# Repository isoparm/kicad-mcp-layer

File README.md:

# kicad-mcp-layer

An AI layer for KiCad 10: a Model Context Protocol server that lets Claude Code, or any MCP
client, work on KiCad designs.

It drives KiCad through three channels and says which one it is using:

| Channel | Mechanism | Used for |
|---|---|---|
| `cli` | `kicad-cli` subprocess | ERC, DRC, netlists, BOM, renders, fabrication exports. Works with KiCad open or closed. |
| `ipc` | KiCad's official IPC API via `kicad-python` | The board open in the PCB editor. Edits land as undo steps. |
| `file` | Lossless edits of `.kicad_sch` and `.kicad_pro` | Schematics, which KiCad 10 exposes no API for. |

The legacy SWIG `pcbnew` module is never used; a test enforces it.

This is the library half of **[kicad-ai-stack](https://github.com/ShamanAndrey/kicad-ai-stack)**, the
workspace it was built in. The stack adds the one-command setup (`bootstrap.py`, which clones this
repository, builds its environment and registers the server with Claude Code) and the working rules for
a session. Start there if you want the whole thing set up; start here if you want the server or the
design package on their own.

## What this is

Two layers on one core.

* **`kicad_layer.design` is the product.** A board is Python data: parts from a catalogue, a
  signal table, circuits as pin-to-net statements, placement, saved copper. The KiCad files are
  build outputs, and KiCad's own ERC and DRC are the tests. Two boards live on it.
* **The MCP server is its check-and-view layer** for Claude Code: checks, exports, renders,
  reviews, documentation and library search. That is the `core` tool tier, registered by
  default. The `full` tier adds the schematic and board edit tools and the routers.

A project holds only its data: sheets as circuits, placement, a `Project`, a routing plan for the
pipeline in `kicad_layer.routers`, and the fabrication package from `kicad_layer.design.fab`. The whole
authoring API is on one generated sheet, [docs/design-api.md](docs/design-api.md), so a session reads
that instead of the source; `python -m kicad_layer.design.inspect` answers questions about a built board.

The routers (`kicad_layer.routers`) are frozen: fixes, not features. The intended loop routes by
hand in KiCad and keeps the copper as data. `tests/test_layers.py` enforces the layering.

## Status

Pre-alpha, built in the open. Done so far:

* Rung 0: environment diagnostics, the capability matrix, project discovery, workspace
  confinement, read-only default mode.
* Rung 1: every kicad-cli tool (ERC, DRC, netlist, trace, BOM, fabrication export, board
  render, schematic render).
* Rung 2: reading the board open in KiCad's PCB Editor over the IPC API (summary, items,
  per-net statistics), with every failure classified as unreachable or rejected.
* Writers: a lossless S-expression engine, a library loader, and schematic and board
  writers that generated a complete 89-LED board which passed ERC and DRC with zero
  findings (`examples/hello_world`).
* Milestone 1: a full-text index of every library KiCad can
  see, including a project's own, with `lib_search`, `sym_info`, `fp_info` and `lib_index`.
* Milestone 2: editing existing schematics losslessly. A concrete syntax tree keeps every
  untouched byte; edits are atomic, snapshotted, refused while KiCad holds the lock, and
  validated by ERC and a netlist comparison. Tools: `sch_list_components`, `sch_get_symbol`,
  `sch_set_property`, `sch_add_component`, `sch_wire`, `sch_label`, `sch_mark`, `sch_delete`,
  `sch_annotate`.

* Milestone 3: editing boards. Live through KiCad's API as one undo step per operation,
  read back from KiCad; or losslessly in the file when the board is closed. A board seen
  live is never edited on disk. Tools: `pcb_place_footprint`, `pcb_move_footprint`,
  `pcb_add_track`, `pcb_add_via`, `pcb_add_zone`, `pcb_refill_zones`, `pcb_delete_items`,
  `pcb_save`. KiCad 10's own "create items from text" call is a stub, so live placement
  builds the footprint from the library file pad by pad.

* Milestone 4: design review beyond DRC. `review_board`, `review_schematic` and
  `review_project` produce one report where every check says PASS, WARN, FAIL, INFO or
  UNVERIFIED with its evidence and the source of its limits: DRC and unrouted connections,
  zone fill state, parts outside the outline, manufacturability against JLCPCB's published
  limits, track widths on power nets, zone stitching, decoupling distance, footprints and
  values and annotation, power-net sources, and the honest state of SPICE. The first run
  on the Hello World found its vias below the fab's minimum annular ring, which is why the
  layer's default via is now 0.8 mm. The first run on a real project then caught the review
  itself: PWR_FLAGs never appear in the exported netlist, so the power-source check now
  follows KiCad's ERC rule instead. Checks are documented in
  [docs/review-checks.md](docs/review-checks.md).

* Writers, second round, for the first real product (a Compute Module 5 carrier): hierarchical
  schematics (sheet symbols with pins, hierarchical labels, per-sheet instance paths, multi-unit
  symbols), boards with any even number of copper layers, and project-local symbol and
  footprint libraries. A seven-sheet, four-layer project generated this way passes ERC with
  no findings; KiCad's own ERC and DRC are the tests.

* Documentation layer: `doc_fetch`, `doc_import`, `doc_list`, `doc_text` and `doc_page` keep
  datasheets and reference designs in an indexed library under `research/references` with
  their source URL, date and hash, extract text per page, and render pages to images so
  pinouts, package drawings and tables can be read. When a site answers with a scripted
  download portal or refuses the plain client, an optional headless-Chromium tier
  (`pip install "kicad-mcp-layer[browser]"`) loads the page and takes the download it offers;
  what still fails gets a classified error that says to save the file in a browser and import it.

* Routing checks and parts: `route_check` measures every differential pair on a board (lengths,
  skew against the interface's limit, coupled share, class gap and width, layer changes) and the
  review carries it as `diff_pairs`; `impedance_calc` and `stackup_info` give closed-form estimates
  next to the fab's published geometries for JLCPCB's 4-layer stack-up; `parts_search` checks
  JLCPCB's assembly catalogue for LCSC codes and stock. The first real board's 28 pairs and 30
  special parts went through them before routing started.

* Routing: `route_pairs` routes differential pairs as coupled pairs (escapes planned and reserved
  for every pair first, a heading-aware search that never folds a pair back on itself, mitred
  offsets, a two-via crossover where P would land on the wrong side, tuning bumps for skew);
  `stitch_planes` drops a stub and via from every surface-mount pad on a plane net; `autoroute`
  hands the rest to FreeRouting through a Specctra DSN with the earlier copper protected and
  merges the session back. All three write a routes JSON next to the board rather than touching
  the board, so a design-as-code project re-applies it on every build. The first real board's 21
  routed pairs came out with zero clearance errors; the residual skew sits on the pairs that
  needed a crossover.

* Manufacturing package (milestone 5, PCBWay): `kicad_layer.design.fab` writes the Gerber and drill
  archive, the position file and a BOM in PCBWay's assembly layout from a finished build, and refuses
  a BOM line without a part number. The first real product ordered from it.

* The design package became the product: `kicad_layer.design` holds a board as data (sheets described
  as circuits with a layout plan, a signal table that drives the module sheet and the root, a project
  with its rule set, placements, blocks) and the KiCad files are build outputs. A build writes the
  schematic, the project file with its constraints and net classes, the design rules, runs ERC, exports
  the netlist and checks every sheet against its own description and against a reference netlist, pin
  group for pin group. Fab rule sets for JLCPCB and AISLER (constraints, classes on the fab's published
  pair geometries, its own `.kicad_dru` rules), and `review_board` takes a fab name for its limits.

* Hand layout on a generated schematic: for a board placed and routed by a person in KiCad, the build
  never writes the board. `build.py --seed` writes its first import instead of KiCad's F8, every footprint
  in rows and linked to its symbol; blocks (an anchor footprint, members with offsets, one KiCad group)
  keep parts that belong together, applied by `--blocks`. The routers are frozen: fixes, not features.

* Parts and documents: `doc_sections` and `doc_facts` read a document's index and a part's fact sheet
  (written once from the datasheet, every number with its page); `lib_fetch` brings a symbol, footprint
  and 3D model for an LCSC code from EasyEDA's data, upgraded to KiCad's current format, for the pad-for-pad
  check against the drawing that follows.

Next: bring-up (milestone 6) and per-fab export profiles, driven by the first real product. See
[docs/tools.md](docs/tools.md) for the tool list.

## Requirements

* KiCad 10.0.x (built against 10.0.6, Windows 11). `kicad-cli` ships with it. Upgrade KiCad
  deliberately: the file formats and the API move with each major, `kicad_doctor` reports the
  drift, and the full test suite is the check.
* Python 3.12 or newer.
* `kicad-python` for the IPC channel (the board open in KiCad), as the `ipc` extra. Without it the
  doctor says so and every kicad-cli and file tool still works. Other extras: `parts` (easyeda2kicad
  behind `lib_fetch`), `preview` (PyMuPDF for sheet previews), `browser` (headless Chromium for
  datasheet portals), `dev` (pytest).
* Developed and tested on Windows 11; kicad-cli discovery also knows the macOS bundle and the Linux
  paths. One convenience is Windows-only: `build.py --open` starts KiCad through a scheduled task.

## Install

The quick way is the stack's bootstrap: clone [kicad-ai-stack](https://github.com/ShamanAndrey/kicad-ai-stack)
and run `python bootstrap.py`; it clones this repository next to it, creates the environment, installs the
extras and writes the Claude Code registration. On its own:

With [uv](https://docs.astral.sh/uv/):

```bash
uv sync --extra dev --extra ipc
uv run pytest
```

With pip:

```bash
python -m venv .venv
.venv\Scripts\python -m pip install -e ".[dev,ipc]"
.venv\Scripts\python -m pytest
```

The default run is the fast loop: in parallel, without the slow tests (a full library index, a
whole review, a headless browser) and without the live ones. `pytest -m "not gui"` adds the slow
tests; `pytest -m ""` runs everything and needs KiCad open with its API on. Tests that need
`kicad-cli` skip themselves when it is not installed.

## Register with Claude Code

Put a `.mcp.json` in the directory that holds your KiCad projects:

```json
{
  "mcpServers": {
    "kicad-mcp-layer": {
      "command": "C:\\path\\to\\kicad-mcp-layer\\.venv\\Scripts\\python.exe",
      "args": ["-m", "kicad_layer"],
      "env": {
        "KICAD_LAYER_WORKSPACE": "C:\\path\\to\\your\\kicad\\projects",
        "KICAD_LAYER_MODE": "readonly"
      }
    }
  }
}
```

Register it in one place only. If Claude Code runs inside the Claude desktop app, quit and
relaunch the app after changing MCP configuration; a new session is not enough.

## Configuration

| Variable | Default | Meaning |
|---|---|---|
| `KICAD_LAYER_WORKSPACE` | current directory | Every path must resolve under it |
| `KICAD_LAYER_MODE` | `readonly` | `write` allows design edits |
| `KICAD_CLI` | auto-detected | Explicit path to `kicad-cli`; if set and wrong, that is an error |
| `KICAD_API_SOCKET` | `ipc://%TEMP%\kicad\api.sock` | IPC address, honoured by `kicad-python` |
| `KICAD_LAYER_CACHE_DIR` | `%LOCALAPPDATA%\kicad-mcp-layer\cache` | Netlist and report cache |
| `KICAD_LAYER_LOG` | `INFO` | stderr log level |
| `KICAD_LAYER_TOOLS` | `core` | `core` registers checks, exports, renders, reviews, libraries, documents and board reads; `full` adds the design-edit tools and the routers |

To use the board tools, enable the API in KiCad: Preferences, Plugins, "Enable KiCad API". It
takes effect immediately.

## Design

The architecture decisions and the research behind them live in a companion `research/`
folder (not part of this package): a survey of every existing KiCad MCP server, KiCad 10's
file formats and API surface, and the tests that showed why no existing schematic parser
could be reused. Short version:

* Connectivity comes from `kicad-cli sch export netlist`, never from home-grown wire tracing.
* Every IPC failure is classified as unreachable or rejected; file edits are allowed only when
  unreachable, and never for a board this process has seen live.
* Schematic writes refuse while KiCad holds the editor lock file.
* Verdicts can say `UNVERIFIED`. A missing report is never a pass.
* Two tool tiers: `core` reads, checks, exports, renders, reviews and documents; `full` adds
  design edits and the frozen routers.

## A word to visitors

Everything here stands on KiCad. It is free, open source, and its development is funded by donations.
The KiCad developers have said what they want for the next release, and every item would let this
project grow: an API for the schematic editor, which KiCad 10 does not have, headless use of that API
through kicad-cli, and footprints generated through the API instead of the footprint wizard. Each one
would replace a workaround in this library with a direct call into KiCad.

If this project is useful to you, please visit [kicad.org](https://www.kicad.org/) and
[donate to KiCad](https://www.kicad.org/donate/). That is where the real work happens.

## Related

* [kicad-ai-stack](https://github.com/ShamanAndrey/kicad-ai-stack): the workspace around this library, with
  the setup script and the working rules for a Claude Code session.
* [examples/hello_world](examples/hello_world): a complete board as data on this library, the first one it built.
* [examples/two_layer_basic](examples/two_layer_basic): the smallest complete project on the design package
  (`Circuit`, `Layout`, `Board`, `Project`), a two-layer board.
* [docs/tools.md](docs/tools.md) the tool reference, [docs/design-api.md](docs/design-api.md) the authoring API.

## Acknowledgements

Ideas and, where MIT-licensed, code from
[kicad-mcp-pro](https://github.com/oaslananka/kicad-mcp-pro),
[kicad-happy](https://github.com/aklofas/kicad-happy),
[lamaalrajih/kicad-mcp](https://github.com/lamaalrajih/kicad-mcp) and
[KiCAD-MCP-Server](https://github.com/mixelpixx/KiCAD-MCP-Server); lessons from
[Konnect](https://github.com/mixelpixx/Konnect). Test fixtures are KiCad's own demo projects.

## License

MIT. See [LICENSE](LICENSE).

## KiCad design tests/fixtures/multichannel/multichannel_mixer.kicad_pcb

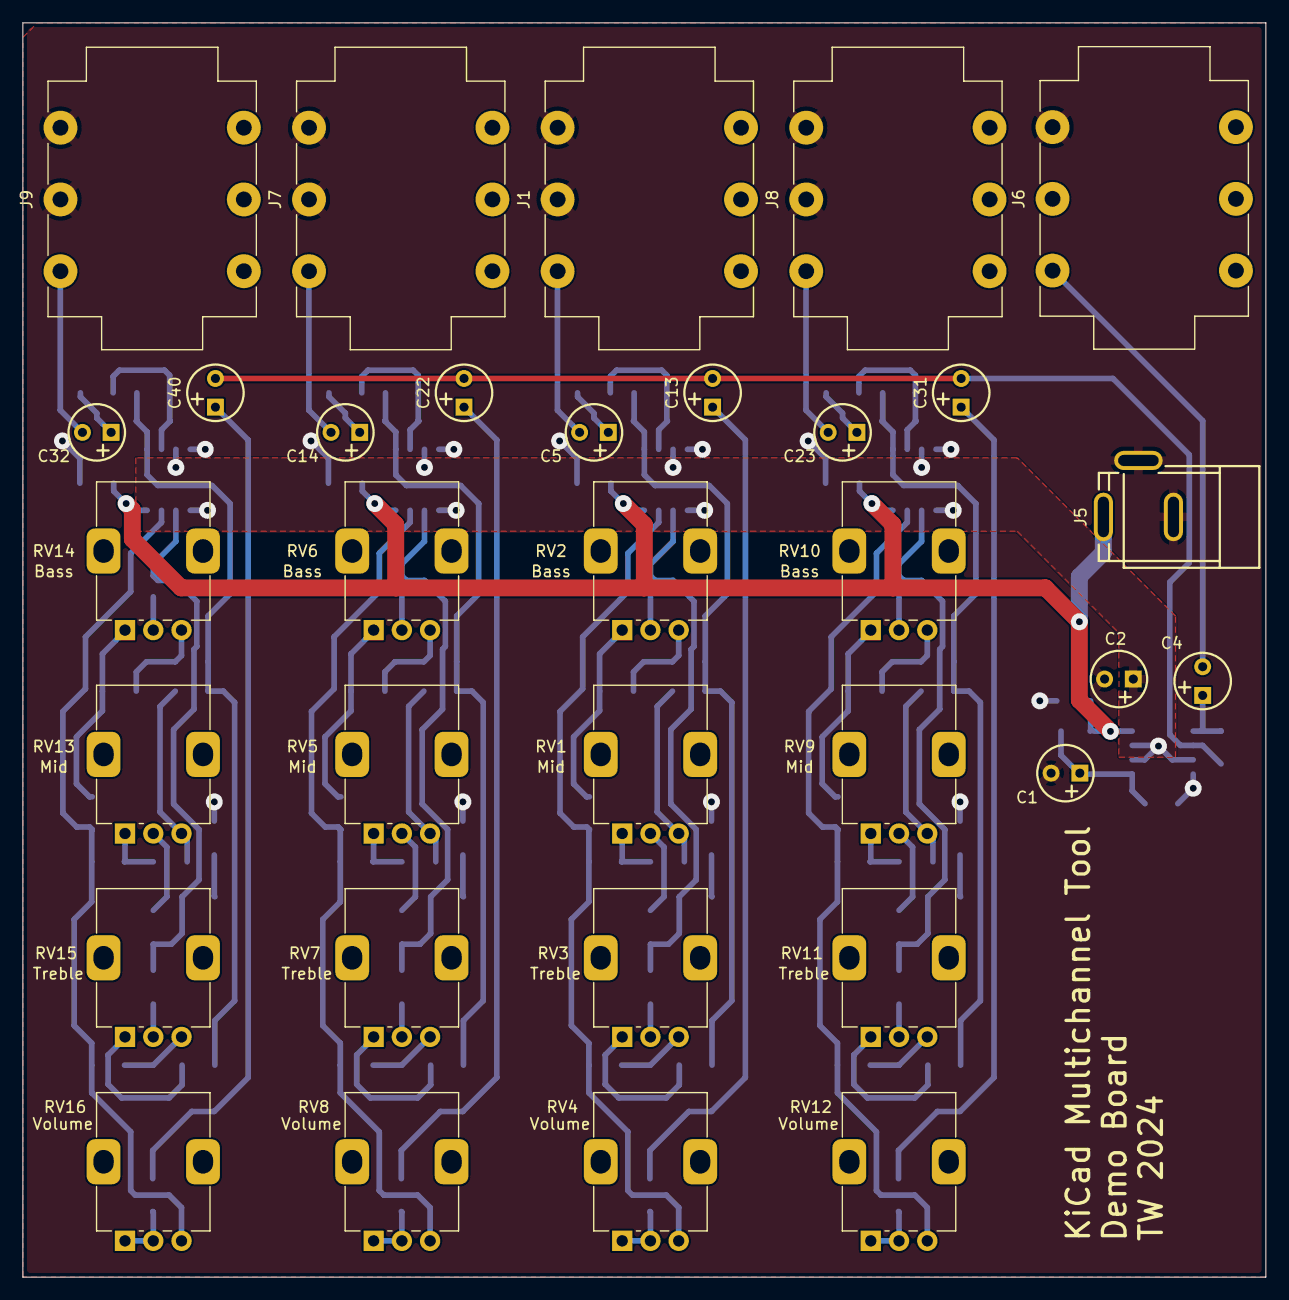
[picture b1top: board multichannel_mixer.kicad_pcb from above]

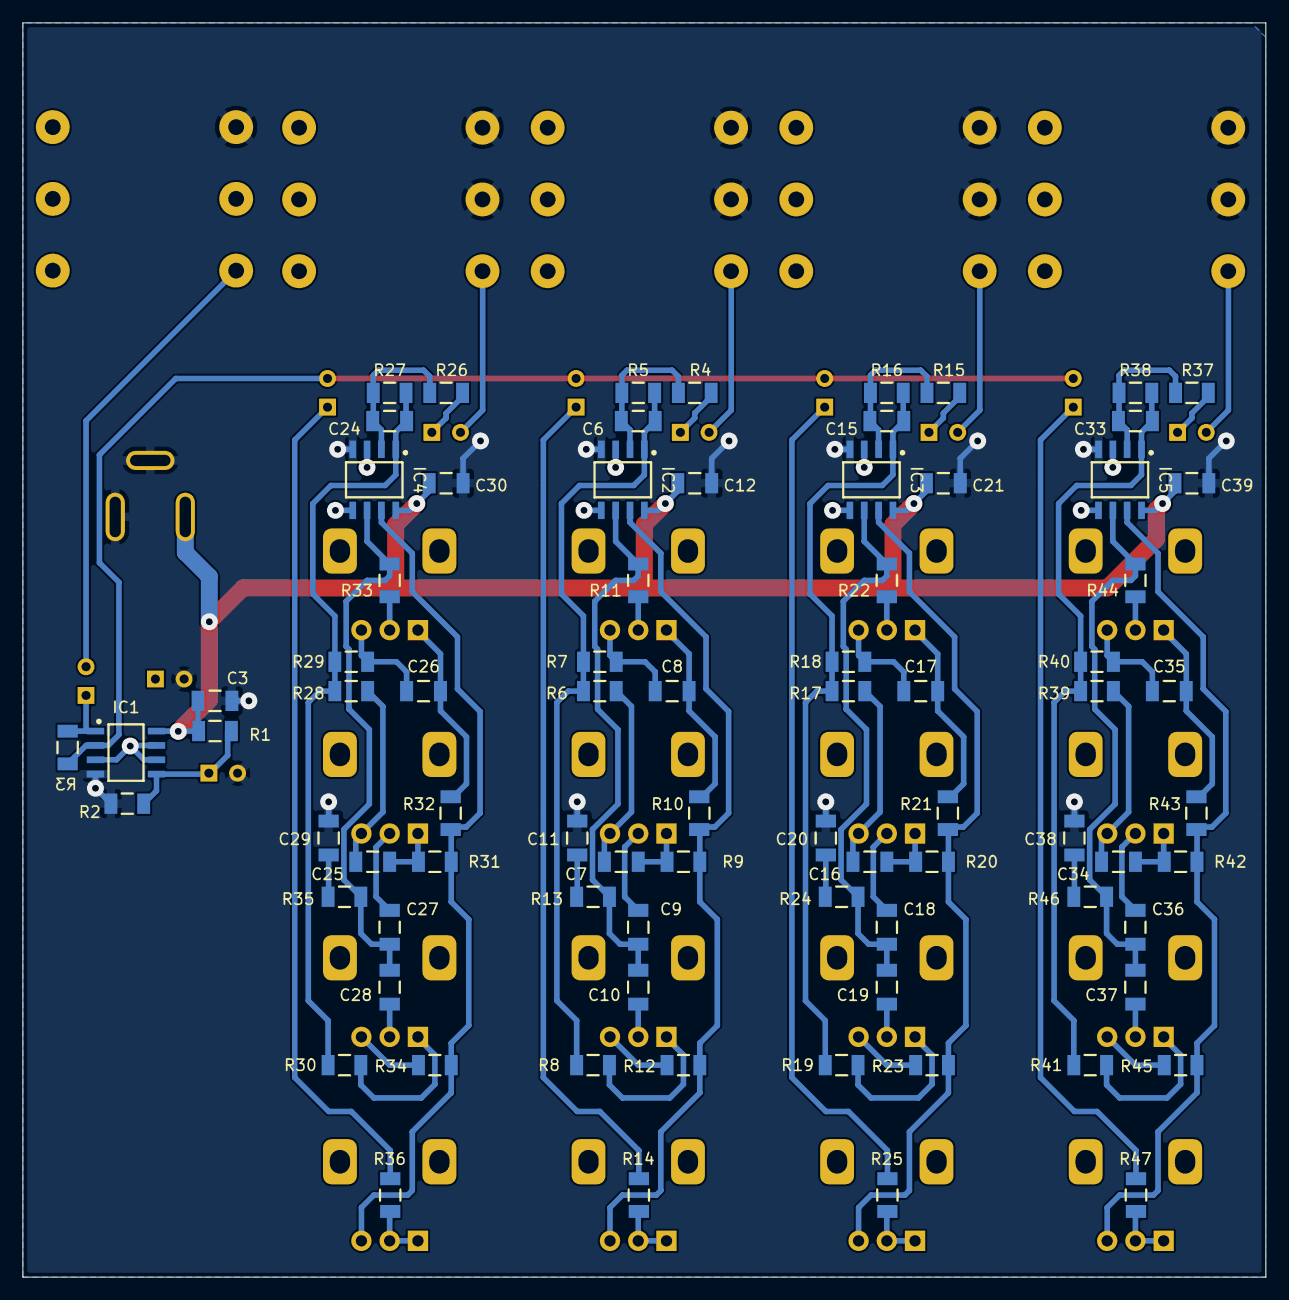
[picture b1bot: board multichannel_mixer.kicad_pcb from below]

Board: 2 copper layers, 110.0 x 111.0 mm, 114 parts (81 on the bottom side), 79 nets.

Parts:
C1, C2, C4, C5, C13, C14, C22, C23, C31, C32, C40: CTEB_2.2UF_35V_10%_254-500X840; CAPPRB254-500X840
C3, C6, C7, C8, C9, C10, C11, C12, C15, C16, C17, C18, C19, C20, C21, C24, C25, C26, C27, C28, C29, C30, C33, C34, C35, C36, C37, C38, C39: CC1206_100NF_50V_10%_X7R; CAPC3216X140N
IC1, IC2, IC3, IC4, IC5: TL072CD; SOIC127P600X175-8N
J1, J6, J7, J8, J9: CH1; Jack_6.35mm_Neutrik_NMJ6HCD2_Horizontal
J5: Power; CLIFF_FC68148(DC-10A)
R1, R2, R3, R4, R5, R6, R7, R8, R9, R10, R11, R12, R13, R14, R15, R16, R17, R18, R19, R20, R21, R22, R23, R24, R25, R26, R27, R28, R29, R30, R31, R32, R33, R34, R35, R36, R37, R38, R39, R40, R41, R42, R43, R44, R45, R46, R47: R1206_10K_1%_0.25W_100PPM; RESC3216X65N
RV1, RV5, RV9, RV13: Mid; Potentiometer_Alps_RK09K_Single_Vertical
RV2, RV6, RV10, RV14: Bass; Potentiometer_Alps_RK09K_Single_Vertical
RV3, RV7, RV11, RV15: Treble; Potentiometer_Alps_RK09K_Single_Vertical
RV4, RV8, RV12, RV16: Volume; Potentiometer_Alps_RK09K_Single_Vertical

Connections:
+12V: C3.2, C12.2, C21.2, C30.2, C39.2, IC1.8 (V+), IC2.8 (V+), IC3.8 (V+), IC4.8 (V+), IC5.8 (V+), J5.1, R1.2
/CH1/OUT: C13.2, C22.2, C31.2, C40.2, IC1.2 (IN-), R3.1
GND: C1.2, C2.2, C3.1, C11.1, C12.1, C20.1, C21.1, C29.1, C30.1, C38.1, C39.1, IC1.4 (V-), IC2.4 (V-), IC3.4 (V-), IC4.4 (V-), IC5.4 (V-), J1.R, J1.S, J5.2, J5.3, J6.S, J7.R, J7.S, J8.R, J8.S, J9.R, J9.S, R2.1
unnamed: C4.2, J6.T
unnamed: C5.1, R4.1
unnamed: C5.2, J1.T
unnamed: C7.1, R6.2, RV1.3
unnamed: C7.2, R9.1, RV1.1
unnamed: C8.1, R7.2, RV2.3
unnamed: C8.2, R10.1, RV2.1
unnamed: C9.1, RV1.2
unnamed: C10.1, RV3.2
unnamed: C11.2, R13.1
unnamed: C13.1, R14.2
unnamed: C14.1, R15.1
unnamed: C14.2, J7.T
unnamed: C16.1, R17.2, RV5.3
unnamed: C16.2, R20.1, RV5.1
unnamed: C17.1, R18.2, RV6.3
unnamed: C17.2, R21.1, RV6.1
unnamed: C18.1, RV5.2
unnamed: C19.1, RV7.2
unnamed: C20.2, R24.1
unnamed: C22.1, R25.2
unnamed: C23.1, R26.1
unnamed: C23.2, J8.T
unnamed: C25.1, R28.2, RV9.3
unnamed: C25.2, R31.1, RV9.1
unnamed: C26.1, R29.2, RV10.3
unnamed: C26.2, R32.1, RV10.1
unnamed: C27.1, RV9.2
unnamed: C28.1, RV11.2
unnamed: C29.2, R35.1
unnamed: C31.1, R36.2
unnamed: C32.1, R37.1
unnamed: C32.2, J9.T
unnamed: C34.1, R39.2, RV13.3
unnamed: C34.2, R42.1, RV13.1
unnamed: C35.1, R40.2, RV14.3
unnamed: C35.2, R43.1, RV14.1
unnamed: C36.1, RV13.2
unnamed: C37.1, RV15.2
unnamed: C38.2, R46.1
unnamed: C40.1, R47.2
unnamed: C4.1, IC1.1 (OUT), R3.2
unnamed: C1.1, IC1.5 (IN+), R1.1, R2.2
unnamed: C6.1, IC2.2 (IN-), R4.2, R5.1
unnamed: C6.2, IC2.1 (OUT), R5.2, R6.1, R7.1, R8.2
unnamed: C9.2, C10.2, IC2.6 (IN-), R11.2, R13.2
unnamed: IC2.7 (OUT), R9.2, R10.2, R12.1, RV4.3
unnamed: C15.1, IC3.2 (IN-), R15.2, R16.1
unnamed: C15.2, IC3.1 (OUT), R16.2, R17.1, R18.1, R19.2
unnamed: C18.2, C19.2, IC3.6 (IN-), R22.2, R24.2
unnamed: IC3.7 (OUT), R20.2, R21.2, R23.1, RV8.3
unnamed: C24.1, IC4.2 (IN-), R26.2, R27.1
unnamed: C24.2, IC4.1 (OUT), R27.2, R28.1, R29.1, R30.2
unnamed: C27.2, C28.2, IC4.6 (IN-), R33.2, R35.2
unnamed: IC4.7 (OUT), R31.2, R32.2, R34.1, RV12.3
unnamed: C33.1, IC5.2 (IN-), R37.2, R38.1
unnamed: C33.2, IC5.1 (OUT), R38.2, R39.1, R40.1, R41.2
unnamed: C36.2, C37.2, IC5.6 (IN-), R44.2, R46.2
unnamed: IC5.7 (OUT), R42.2, R43.2, R45.1, RV16.3
unnamed: R8.1, RV3.1
unnamed: R11.1, RV2.2
unnamed: R12.2, RV3.3
unnamed: R14.1, RV4.1, RV4.2
unnamed: R19.1, RV7.1
unnamed: R22.1, RV6.2
unnamed: R23.2, RV7.3
unnamed: R25.1, RV8.1, RV8.2
unnamed: R30.1, RV11.1
unnamed: R33.1, RV10.2
unnamed: R34.2, RV11.3
unnamed: R36.1, RV12.1, RV12.2
unnamed: R41.1, RV15.1
unnamed: R44.1, RV14.2
unnamed: R45.2, RV15.3
unnamed: R47.1, RV16.1, RV16.2
vbias: C2.1, IC1.3 (IN+), IC1.6 (IN-), IC1.7 (OUT), IC2.3 (IN+), IC2.5 (IN+), IC3.3 (IN+), IC3.5 (IN+), IC4.3 (IN+), IC4.5 (IN+), IC5.3 (IN+), IC5.5 (IN+)

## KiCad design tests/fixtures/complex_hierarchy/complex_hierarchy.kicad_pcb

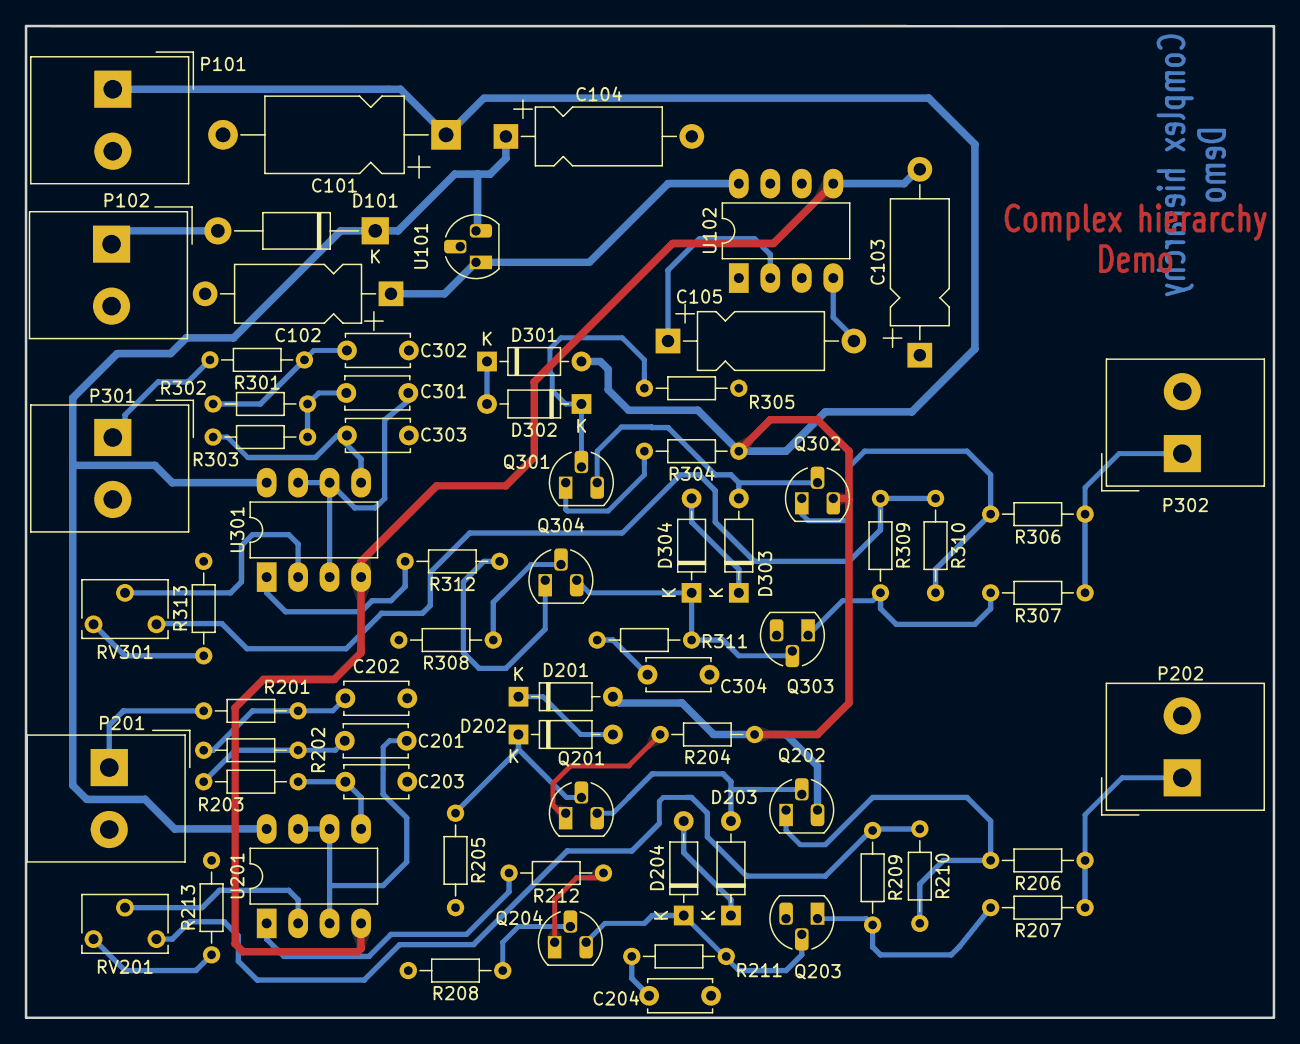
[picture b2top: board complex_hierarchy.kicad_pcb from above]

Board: 2 copper layers, 100.7 x 80.0 mm, 68 parts (0 on the bottom side), 50 nets.

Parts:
C101: 47uF/63V; CP_Axial_L11.0mm_D6.0mm_P18.00mm_Horizontal
C102: 47uF; CP_Axial_L10.0mm_D4.5mm_P15.00mm_Horizontal
C103, C105: 10uF; CP_Axial_L10.0mm_D4.5mm_P15.00mm_Horizontal
C104: 47uF/20V; CP_Axial_L10.0mm_D4.5mm_P15.00mm_Horizontal
C201, C301: 15nF; C_Disc_D5.0mm_W2.5mm_P5.00mm
C202, C302: 150nF; C_Disc_D5.0mm_W2.5mm_P5.00mm
C203, C303: 4.7nF; C_Disc_D5.0mm_W2.5mm_P5.00mm
C204, C304: 820pF; C_Disc_D5.0mm_W2.5mm_P5.00mm
D101: 1N4007; D_DO-41_SOD81_P12.70mm_Horizontal
D201, D202, D203, D204, D301, D302, D303, D304: 1N4148; D_DO-35_SOD27_P7.62mm_Horizontal
P101, P102, P201, P202, P301, P302: CONN_2; Altech_AK300_1x02_P5.00mm_45-Degree
Q201, Q203, Q301, Q303: MPSA92; TO-92_HandSolder
Q202, Q204, Q302, Q304: MPSA42; TO-92_HandSolder
R201, R208, R212, R301, R308, R312: 1K; R_Axial_DIN0204_L3.6mm_D1.6mm_P7.62mm_Horizontal
R202, R203, R302, R303: 22K; R_Axial_DIN0204_L3.6mm_D1.6mm_P7.62mm_Horizontal
R204, R304: 470; R_Axial_DIN0204_L3.6mm_D1.6mm_P7.62mm_Horizontal
R205, R209, R210, R305, R309, R310: 220K; R_Axial_DIN0204_L3.6mm_D1.6mm_P7.62mm_Horizontal
R206, R207, R306, R307: 47; R_Axial_DIN0204_L3.6mm_D1.6mm_P7.62mm_Horizontal
R211, R311: 5,6K; R_Axial_DIN0204_L3.6mm_D1.6mm_P7.62mm_Horizontal
R213, R313: 4,7K; R_Axial_DIN0204_L3.6mm_D1.6mm_P7.62mm_Horizontal
RV201, RV301: 4,7K; Potentiometer_Bourns_3266W_Vertical
U101: 78L05; TO-92_HandSolder
U102: ICL7660; DIP-8_W7.62mm_LongPads
U201, U301: LM358N; DIP-8_W7.62mm_LongPads

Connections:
+12V: C104.1, D101.1 (K), U101.3 (VI), U201.8 (V+), U301.8 (V+)
-VAA: C103.2, U102.5 (VOUT), U201.4 (V-), U301.4 (V-)
/12Vext: D101.2 (A), P102.1
/ampli_ht_horizontal/PIEZO_IN: P301.1, R301.2
/ampli_ht_horizontal/PIEZO_OUT: P302.1, R306.1, R307.1
/ampli_ht_horizontal/S_OUT+: R309.1, R310.1, RV301.3
/ampli_ht_horizontal/Vpil_0_3,3V: C301.1, U301.3 (+), U301.6 (-), U301.7
/ampli_ht_vertical/PIEZO_IN: P201.1, R201.2
/ampli_ht_vertical/PIEZO_OUT: P202.1, R206.1, R207.1
/ampli_ht_vertical/S_OUT+: R209.1, R210.1, RV201.3
/ampli_ht_vertical/Vpil_0_3,3V: C201.1, U201.3 (+), U201.6 (-), U201.7
GND: C101.2, C102.2, C103.1, C104.2, C202.2, C203.2, C204.2, C302.2, C303.2, C304.2, P101.2 (PM), P102.2 (PM), P201.2 (PM), P202.2 (PM), P301.2 (PM), P302.2 (PM), Q203.3 (C), Q303.3 (C), R205.2, R208.2, R213.2, R305.2, R308.2, R313.2, U101.2 (GND), U102.3 (GND)
HT: C101.1, D201.2 (A), D301.2 (A), P101.1, Q202.3 (C), Q302.3 (C), R204.1, R304.1
unnamed: C201.2, R202.1, R203.2
unnamed: C202.1, R201.1, R202.2
unnamed: C204.1, R211.2
unnamed: C301.2, R302.1, R303.2
unnamed: C302.1, R301.1, R302.2
unnamed: C304.1, R311.2
unnamed: D201.1 (K), D202.2 (A)
unnamed: D202.1 (K), Q201.2 (B), R205.1
unnamed: D203.2 (A), Q201.3 (C), Q202.2 (B)
unnamed: D203.1 (K), D204.2 (A)
unnamed: D204.1 (K), Q203.2 (B), Q204.3 (C), R211.1
unnamed: D301.1 (K), D302.2 (A)
unnamed: D302.1 (K), Q301.2 (B), R305.1
unnamed: D303.2 (A), Q301.3 (C), Q302.2 (B)
unnamed: D303.1 (K), D304.2 (A)
unnamed: D304.1 (K), Q303.2 (B), Q304.3 (C), R311.1
unnamed: Q201.1 (E), R204.2
unnamed: Q202.1 (E), R206.2, R210.2
unnamed: Q203.1 (E), R207.2, R209.2
unnamed: Q204.2 (B), R208.1
unnamed: Q204.1 (E), R212.1
unnamed: Q301.1 (E), R304.2
unnamed: Q302.1 (E), R306.2, R310.2
unnamed: Q303.1 (E), R307.2, R309.2
unnamed: Q304.2 (B), R308.1
unnamed: Q304.1 (E), R312.1
unnamed: R212.2, U201.1
unnamed: R213.1, RV201.1
unnamed: R312.2, U301.1
unnamed: R313.1, RV301.1
unnamed: C105.1, U102.2 (CAP+)
unnamed: C105.2, U102.4 (CAP-)
unnamed: RV201.2, U201.2 (-)
unnamed: C203.1, R203.1, U201.5 (+)
unnamed: RV301.2, U301.2 (-)
unnamed: C303.1, R303.1, U301.5 (+)
VCC: C102.1, U101.1 (VO), U102.8 (V+)

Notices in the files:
parts and their libraries:
License: This work is licensed under the Creative Commons CC-BY-SA 4.0 License. To the extent that circuit schematics that use Licensed Material can be considered to be ‘Adapted Material’, then the copyright holder waives article 3.b of the license with respect to these schematics.
